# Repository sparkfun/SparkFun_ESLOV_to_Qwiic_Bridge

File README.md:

SparkFun ESLOV to Qwiic Bridge
========================================

[*SparkFun ESLOV to Qwiic Bridge (BOB-23589)*](https://www.sparkfun.com/products/23589)

The SparkFun ESLOV to Qwiic Bridge lets you quickly and easily connect Qwiic breakouts to Arduino boards with an ESLOV connector for I2C communication. ESLOV and Qwiic allow for simple assembly of I2C circuits without requiring soldering.

The ESLOV to Qwiic Bridge includes one Qwiic connector and one ESLOV connector, along with a plated through hole for the interrupt pin on the ESLOV connection. Since the ESLOV connectors have 5V for power, this bridge board includes a voltage regulator to drop that 5V down to 3.3V, making it safe for any Qwiic device.

Repository Contents
-------------------

* **/Documentation** - Data sheets, additional product information
* **/Hardware** - Eagle design files (.brd, .sch)
* **/Production** - Production panel files (.brd)

Product Versions
----------------
* [BOB-23589](https://www.sparkfun.com/products/23589) - Initial release of SparkFun ESLOV to Qwiic Bridge

License Information
-------------------

This product is _**open source**_! 

Please review the LICENSE.md file for license information. 

If you have any questions or concerns on licensing, please contact technical support on our [SparkFun forums](https://forum.sparkfun.com/viewforum.php?f=152).

Distributed as-is; no warranty is given.

- Your friends at SparkFun.

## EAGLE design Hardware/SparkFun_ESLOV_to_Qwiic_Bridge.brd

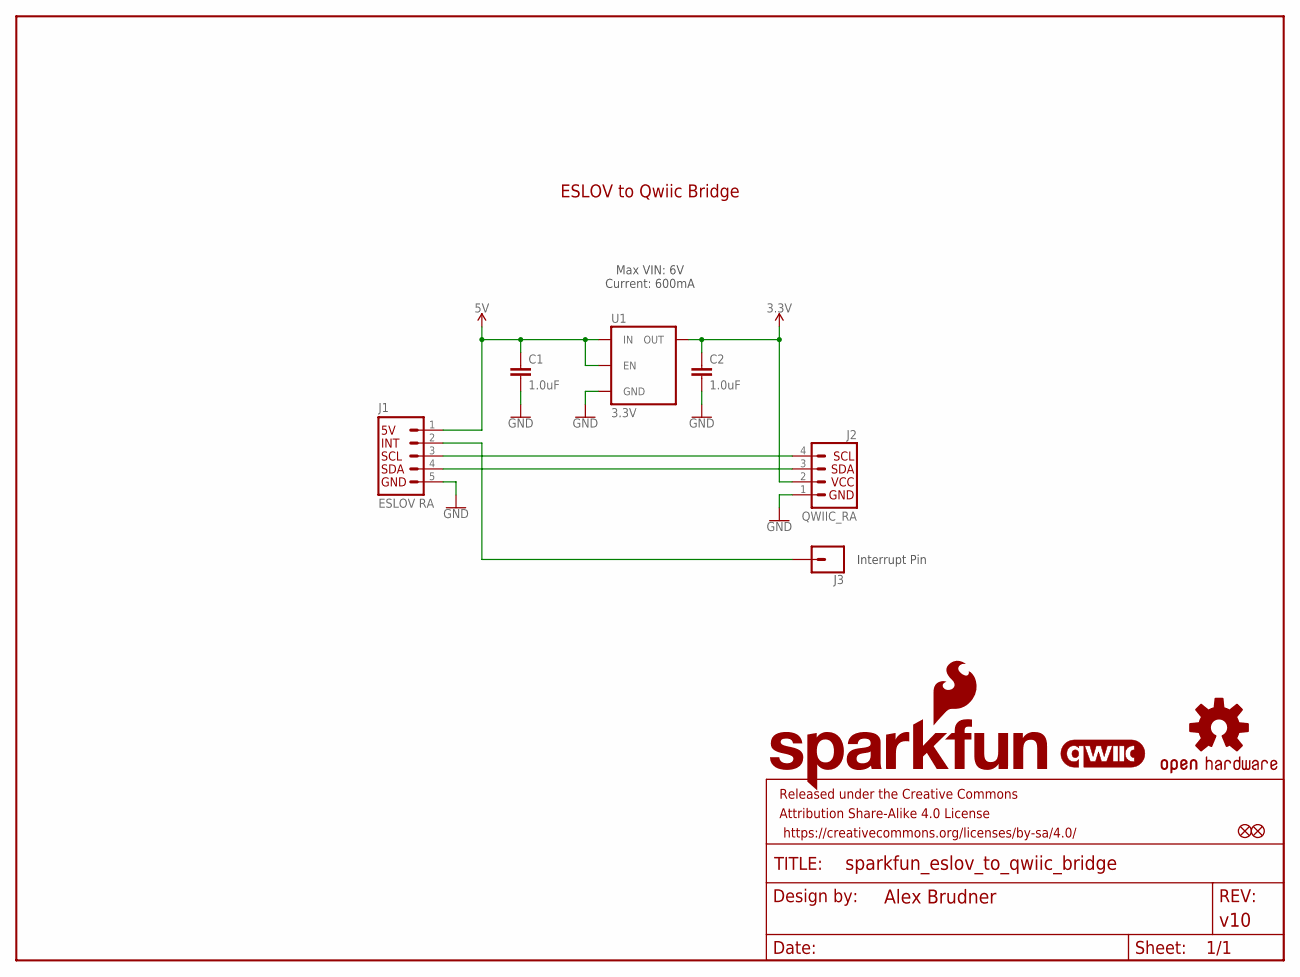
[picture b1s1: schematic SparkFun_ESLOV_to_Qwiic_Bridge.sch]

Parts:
C1, C2: 1.0uF; 0402-TIGHT
FD1, FD2: FIDUCIALUFIDUCIAL; FIDUCIAL-MICRO
FRAME1: FRAME-LETTER; CREATIVE_COMMONS
J1: ESLOV RA; JST_5_1MM_RA
J2: QWIIC_RA; JST04_1MM_RA
J3: CONN_01; 1X01
LOGO1: SFE_LOGO_NAME_FLAME.1_INCH; SFE_LOGO_NAME_FLAME_.1
LOGO2: OSHW-LOGOMINI; OSHW-LOGO-MINI
LOGO3: QWIIC_LOGO_CONNECTOR; QWIIC_5.5MM
U1: 3.3V; SOT23-5

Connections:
3.3V: C2.1, J2.2, U1.5 (OUT)
5V: C1.1, J1.1, U1.1 (IN), U1.3 (EN)
GND: C1.2, C2.2, J1.5, J2.1, U1.2 (GND)
INT: J1.2, J3.1
SCL: J1.3, J2.4
SDA: J1.4, J2.3

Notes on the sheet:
ESLOV to Qwiic Bridge
Interrupt Pin
Max VIN: 6V Current: 600mA

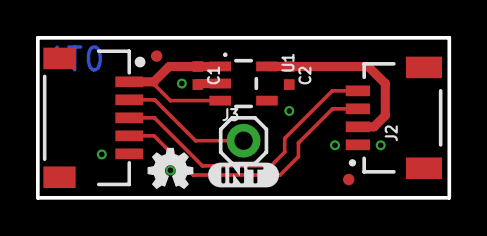
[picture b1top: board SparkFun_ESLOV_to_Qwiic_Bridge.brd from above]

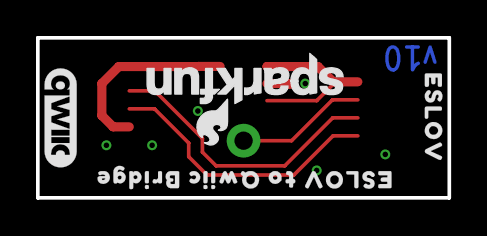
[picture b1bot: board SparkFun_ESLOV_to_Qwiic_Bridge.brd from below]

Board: 2 copper layers, 22.9 x 8.9 mm, 17 parts (4 on the bottom side), 6 nets.

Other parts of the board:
U$1: #INT#0
U$2: ESLOV0
U$3: SFE_LOGO_FLAME_STOP_.1
U$4: ESLOV_TO_QWIIC_BRIDGE0
U$5: ORDERING_INSTRUCTIONS

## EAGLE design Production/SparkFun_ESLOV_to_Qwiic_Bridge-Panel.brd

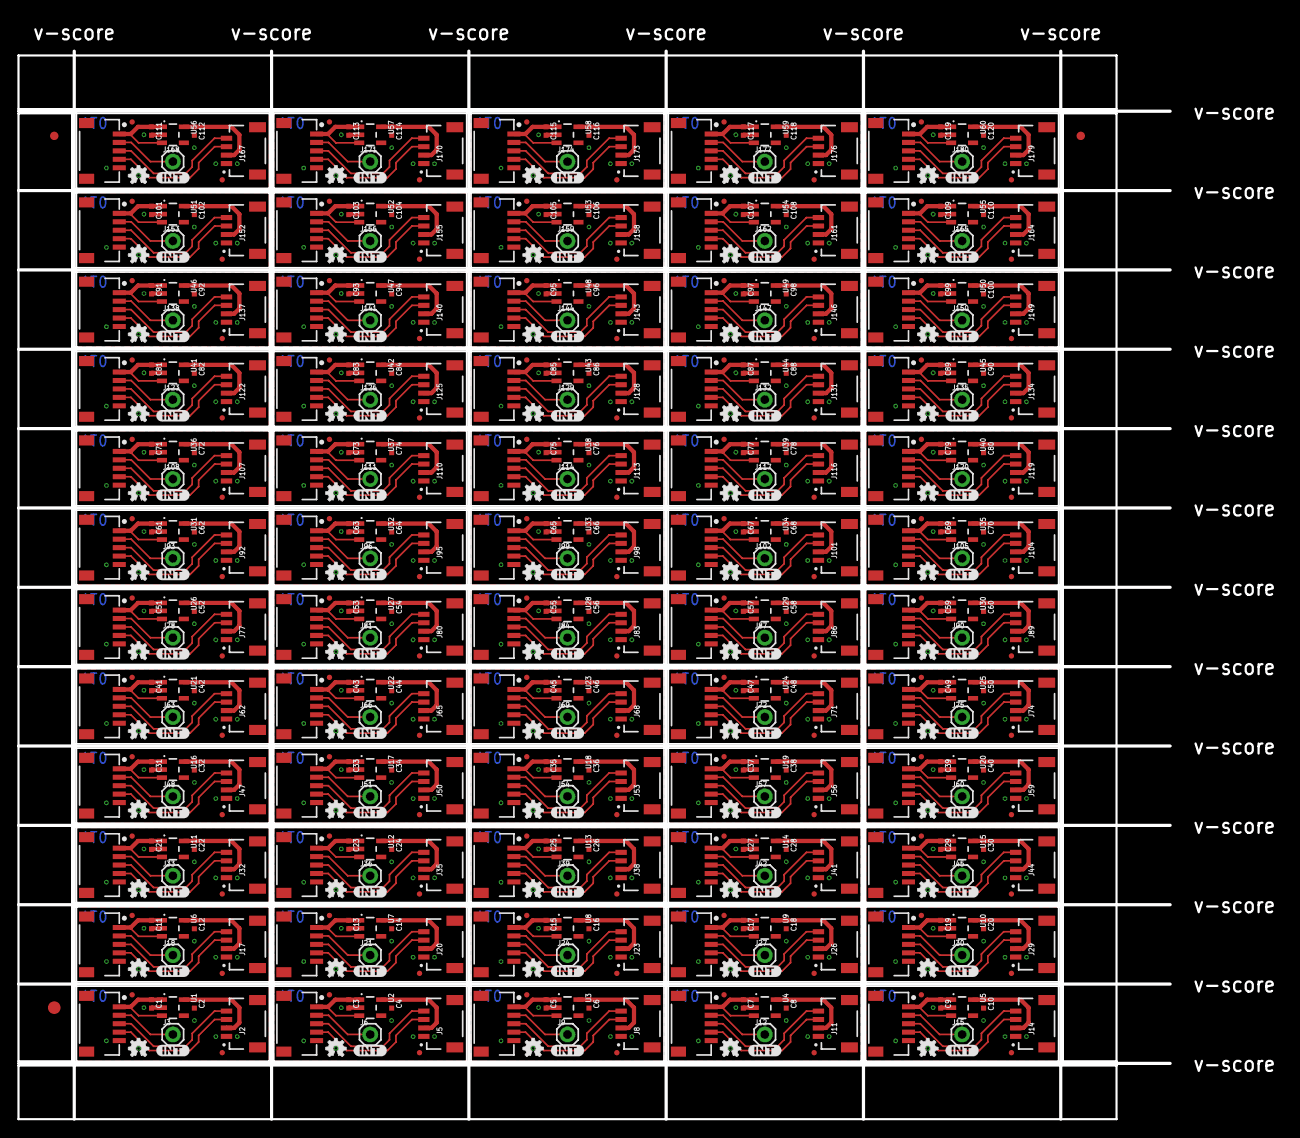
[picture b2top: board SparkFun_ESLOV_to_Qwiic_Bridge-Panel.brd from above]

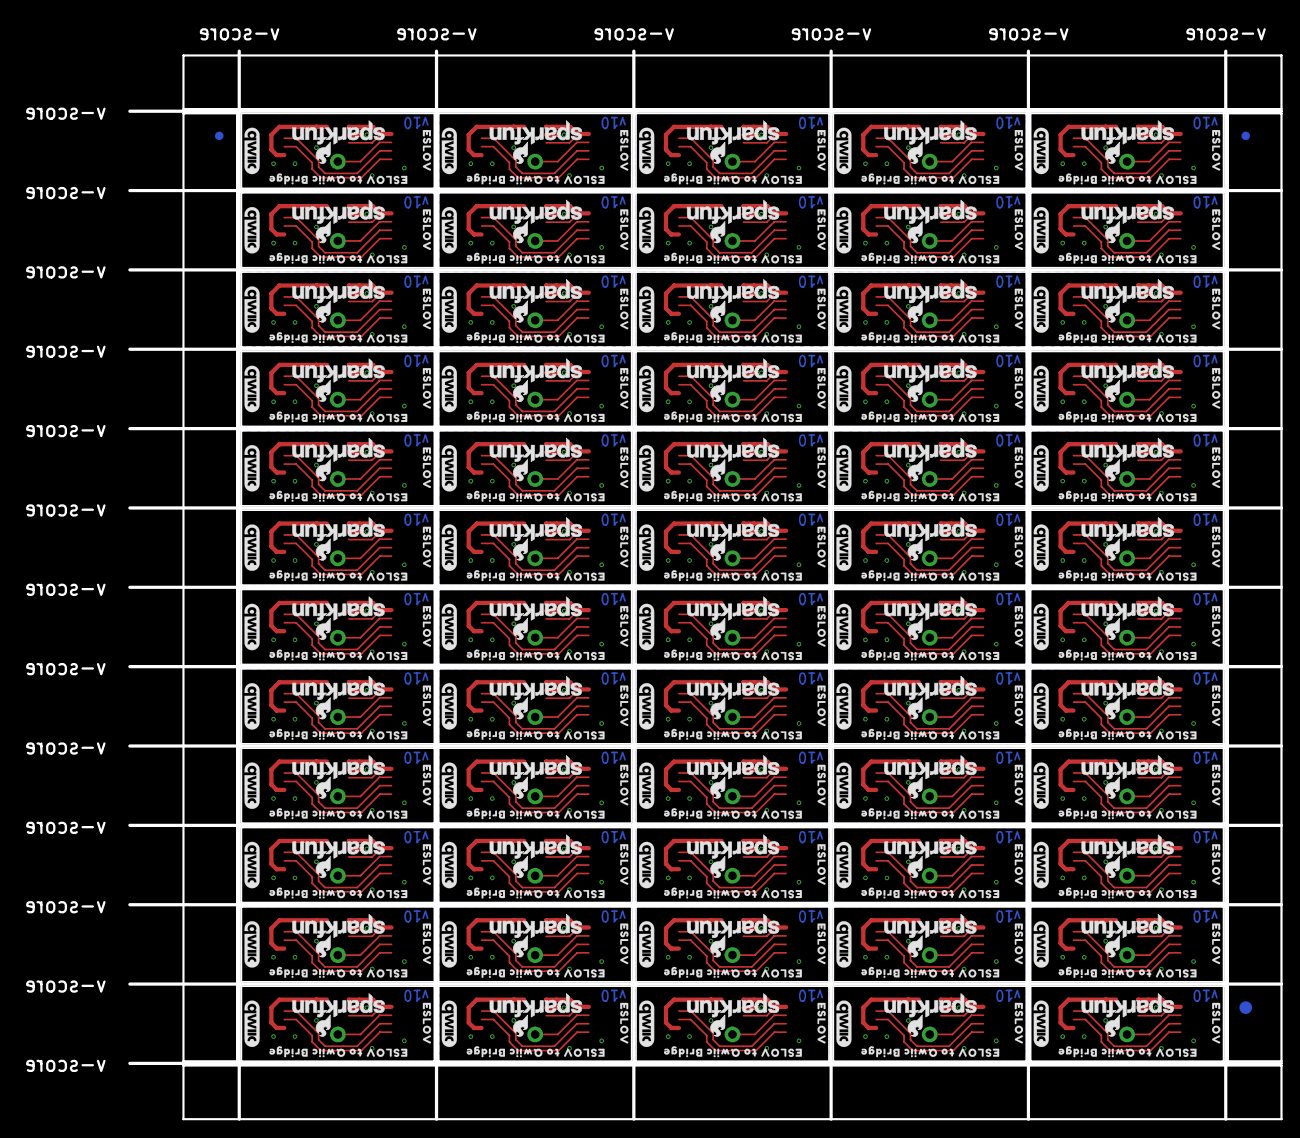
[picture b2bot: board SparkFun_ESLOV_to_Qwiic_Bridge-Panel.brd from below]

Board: 2 copper layers, 136.4 x 126.5 mm, 906 parts (243 on the bottom side), 360 nets.

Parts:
C1, C2, C3, C4, C5, C6, C7, C8, C9, C10, C11, C12, C13, C14, C15, C16, C17, C18, C19, C20, C21, C22, C23, C24, C25, C26, C27, C28, C29, C30, C31, C32, C33, C34, C35, C36, C37, C38, C39, C40, C41, C42, C43, C44, C45, C46, C47, C48, C49, C50, C51, C52, C53, C54, C55, C56, C57, C58, C59, C60, C61, C62, C63, C64, C65, C66, C67, C68, C69, C70, C71, C72, C73, C74, C75, C76, C77, C78, C79, C80, C81, C82, C83, C84, C85, C86, C87, C88, C89, C90, C91, C92, C93, C94, C95, C96, C97, C98, C99, C100, C101, C102, C103, C104, C105, C106, C107, C108, C109, C110, C111, C112, C113, C114, C115, C116, C117, C118, C119, C120: 1.0uF; 0402-TIGHT
E$1, E$2, E$3, E$4: FIDUCIAL-1X2
E$5, E$6: FIDUCIAL-1.5X3
FD1, FD2, FD3, FD4, FD5, FD6, FD7, FD8, FD9, FD10, FD11, FD12, FD13, FD14, FD15, FD16, FD17, FD18, FD19, FD20, FD21, FD22, FD23, FD24, FD25, FD26, FD27, FD28, FD29, FD30, FD31, FD32, FD33, FD34, FD35, FD36, FD37, FD38, FD39, FD40, FD41, FD42, FD43, FD44, FD45, FD46, FD47, FD48, FD49, FD50, FD51, FD52, FD53, FD54, FD55, FD56, FD57, FD58, FD59, FD60, FD61, FD62, FD63, FD64, FD65, FD66, FD67, FD68, FD69, FD70, FD71, FD72, FD73, FD74, FD75, FD76, FD77, FD78, FD79, FD80, FD81, FD82, FD83, FD84, FD85, FD86, FD87, FD88, FD89, FD90, FD91, FD92, FD93, FD94, FD95, FD96, FD97, FD98, FD99, FD100, FD101, FD102, FD103, FD104, FD105, FD106, FD107, FD108, FD109, FD110, FD111, FD112, FD113, FD114, FD115, FD116, FD117, FD118, FD119, FD120: FIDUCIALUFIDUCIAL; FIDUCIAL-MICRO
J1, J4, J7, J10, J13, J16, J19, J22, J25, J28, J31, J34, J37, J40, J43, J46, J49, J52, J55, J58, J61, J64, J67, J70, J73, J76, J79, J82, J85, J88, J91, J94, J97, J100, J103, J106, J109, J112, J115, J118, J121, J124, J127, J130, J133, J136, J139, J142, J145, J148, J151, J154, J157, J160, J163, J166, J169, J172, J175, J178: ESLOV RA; JST_5_1MM_RA
J2, J5, J8, J11, J14, J17, J20, J23, J26, J29, J32, J35, J38, J41, J44, J47, J50, J53, J56, J59, J62, J65, J68, J71, J74, J77, J80, J83, J86, J89, J92, J95, J98, J101, J104, J107, J110, J113, J116, J119, J122, J125, J128, J131, J134, J137, J140, J143, J146, J149, J152, J155, J158, J161, J164, J167, J170, J173, J176, J179: QWIIC_RA; JST04_1MM_RA
J3, J6, J9, J12, J15, J18, J21, J24, J27, J30, J33, J36, J39, J42, J45, J48, J51, J54, J57, J60, J63, J66, J69, J72, J75, J78, J81, J84, J87, J90, J93, J96, J99, J102, J105, J108, J111, J114, J117, J120, J123, J126, J129, J132, J135, J138, J141, J144, J147, J150, J153, J156, J159, J162, J165, J168, J171, J174, J177, J180: 1X01
LOGO1, LOGO4, LOGO7, LOGO10, LOGO13, LOGO16, LOGO19, LOGO22, LOGO25, LOGO28, LOGO31, LOGO34, LOGO37, LOGO40, LOGO43, LOGO46, LOGO49, LOGO52, LOGO55, LOGO58, LOGO61, LOGO64, LOGO67, LOGO70, LOGO73, LOGO76, LOGO79, LOGO82, LOGO85, LOGO88, LOGO91, LOGO94, LOGO97, LOGO100, LOGO103, LOGO106, LOGO109, LOGO112, LOGO115, LOGO118, LOGO121, LOGO124, LOGO127, LOGO130, LOGO133, LOGO136, LOGO139, LOGO142, LOGO145, LOGO148, LOGO151, LOGO154, LOGO157, LOGO160, LOGO163, LOGO166, LOGO169, LOGO172, LOGO175, LOGO178: SFE_LOGO_NAME_FLAME.1_INCH; SFE_LOGO_NAME_FLAME_.1
LOGO2, LOGO5, LOGO8, LOGO11, LOGO14, LOGO17, LOGO20, LOGO23, LOGO26, LOGO29, LOGO32, LOGO35, LOGO38, LOGO41, LOGO44, LOGO47, LOGO50, LOGO53, LOGO56, LOGO59, LOGO62, LOGO65, LOGO68, LOGO71, LOGO74, LOGO77, LOGO80, LOGO83, LOGO86, LOGO89, LOGO92, LOGO95, LOGO98, LOGO101, LOGO104, LOGO107, LOGO110, LOGO113, LOGO116, LOGO119, LOGO122, LOGO125, LOGO128, LOGO131, LOGO134, LOGO137, LOGO140, LOGO143, LOGO146, LOGO149, LOGO152, LOGO155, LOGO158, LOGO161, LOGO164, LOGO167, LOGO170, LOGO173, LOGO176, LOGO179: OSHW-LOGOMINI; OSHW-LOGO-MINI
LOGO3, LOGO6, LOGO9, LOGO12, LOGO15, LOGO18, LOGO21, LOGO24, LOGO27, LOGO30, LOGO33, LOGO36, LOGO39, LOGO42, LOGO45, LOGO48, LOGO51, LOGO54, LOGO57, LOGO60, LOGO63, LOGO66, LOGO69, LOGO72, LOGO75, LOGO78, LOGO81, LOGO84, LOGO87, LOGO90, LOGO93, LOGO96, LOGO99, LOGO102, LOGO105, LOGO108, LOGO111, LOGO114, LOGO117, LOGO120, LOGO123, LOGO126, LOGO129, LOGO132, LOGO135, LOGO138, LOGO141, LOGO144, LOGO147, LOGO150, LOGO153, LOGO156, LOGO159, LOGO162, LOGO165, LOGO168, LOGO171, LOGO174, LOGO177, LOGO180: QWIIC_LOGO_CONNECTOR; QWIIC_5.5MM
U1, U2, U3, U4, U5, U6, U7, U8, U9, U10, U11, U12, U13, U14, U15, U16, U17, U18, U19, U20, U21, U22, U23, U24, U25, U26, U27, U28, U29, U30, U31, U32, U33, U34, U35, U36, U37, U38, U39, U40, U41, U42, U43, U44, U45, U46, U47, U48, U49, U50, U51, U52, U53, U54, U55, U56, U57, U58, U59, U60: 3.3V; SOT23-5
U$1, U$5, U$9, U$13, U$17, U$21, U$25, U$29, U$33, U$37, U$41, U$45, U$49, U$53, U$57, U$61, U$65, U$69, U$73, U$77, U$81, U$85, U$89, U$93, U$97, U$101, U$105, U$109, U$113, U$117, U$121, U$125, U$129, U$133, U$137, U$141, U$145, U$149, U$153, U$157, U$161, U$165, U$169, U$173, U$177, U$181, U$185, U$189, U$193, U$197, U$201, U$205, U$209, U$213, U$217, U$221, U$225, U$229, U$233, U$237: #INT#0
U$2, U$7, U$11, U$15, U$19, U$23, U$27, U$31, U$35, U$39, U$43, U$47, U$51, U$55, U$59, U$63, U$67, U$71, U$75, U$79, U$83, U$87, U$91, U$95, U$99, U$103, U$107, U$111, U$115, U$119, U$123, U$127, U$131, U$135, U$139, U$143, U$147, U$151, U$155, U$159, U$163, U$167, U$171, U$175, U$179, U$183, U$187, U$191, U$195, U$199, U$203, U$207, U$211, U$215, U$219, U$223, U$227, U$231, U$235, U$239: ESLOV0
U$3, U$6, U$10, U$14, U$18, U$22, U$26, U$30, U$34, U$38, U$42, U$46, U$50, U$54, U$58, U$62, U$66, U$70, U$74, U$78, U$82, U$86, U$90, U$94, U$98, U$102, U$106, U$110, U$114, U$118, U$122, U$126, U$130, U$134, U$138, U$142, U$146, U$150, U$154, U$158, U$162, U$166, U$170, U$174, U$178, U$182, U$186, U$190, U$194, U$198, U$202, U$206, U$210, U$214, U$218, U$222, U$226, U$230, U$234, U$238: SFE_LOGO_FLAME_STOP_.1
U$4, U$8, U$12, U$16, U$20, U$24, U$28, U$32, U$36, U$40, U$44, U$48, U$52, U$56, U$60, U$64, U$68, U$72, U$76, U$80, U$84, U$88, U$92, U$96, U$100, U$104, U$108, U$112, U$116, U$120, U$124, U$128, U$132, U$136, U$140, U$144, U$148, U$152, U$156, U$160, U$164, U$168, U$172, U$176, U$180, U$184, U$188, U$192, U$196, U$200, U$204, U$208, U$212, U$216, U$220, U$224, U$228, U$232, U$236, U$240: ESLOV_TO_QWIIC_BRIDGE0

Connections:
3.3V: C2.1, J2.2, U1.5
3.3V1: C4.1, J5.2, U2.5
3.3V2: C6.1, J8.2, U3.5
3.3V3: C8.1, J11.2, U4.5
3.3V4: C10.1, J14.2, U5.5
3.3V5: C12.1, J17.2, U6.5
3.3V6: C14.1, J20.2, U7.5
3.3V7: C16.1, J23.2, U8.5
3.3V8: C18.1, J26.2, U9.5
3.3V9: C20.1, J29.2, U10.5
3.3V10: C22.1, J32.2, U11.5
3.3V11: C24.1, J35.2, U12.5
3.3V12: C26.1, J38.2, U13.5
3.3V13: C28.1, J41.2, U14.5
3.3V14: C30.1, J44.2, U15.5
3.3V15: C32.1, J47.2, U16.5
3.3V16: C34.1, J50.2, U17.5
3.3V17: C36.1, J53.2, U18.5
3.3V18: C38.1, J56.2, U19.5
3.3V19: C40.1, J59.2, U20.5
3.3V20: C42.1, J62.2, U21.5
3.3V21: C44.1, J65.2, U22.5
3.3V22: C46.1, J68.2, U23.5
3.3V23: C48.1, J71.2, U24.5
3.3V24: C50.1, J74.2, U25.5
3.3V25: C52.1, J77.2, U26.5
3.3V26: C54.1, J80.2, U27.5
3.3V27: C56.1, J83.2, U28.5
3.3V28: C58.1, J86.2, U29.5
3.3V29: C60.1, J89.2, U30.5
3.3V30: C62.1, J92.2, U31.5
3.3V31: C64.1, J95.2, U32.5
3.3V32: C66.1, J98.2, U33.5
3.3V33: C68.1, J101.2, U34.5
3.3V34: C70.1, J104.2, U35.5
3.3V35: C72.1, J107.2, U36.5
3.3V36: C74.1, J110.2, U37.5
3.3V37: C76.1, J113.2, U38.5
3.3V38: C78.1, J116.2, U39.5
3.3V39: C80.1, J119.2, U40.5
3.3V40: C82.1, J122.2, U41.5
3.3V41: C84.1, J125.2, U42.5
3.3V42: C86.1, J128.2, U43.5
3.3V43: C88.1, J131.2, U44.5
3.3V44: C90.1, J134.2, U45.5
3.3V45: C92.1, J137.2, U46.5
3.3V46: C94.1, J140.2, U47.5
3.3V47: C96.1, J143.2, U48.5
3.3V48: C98.1, J146.2, U49.5
3.3V49: C100.1, J149.2, U50.5
3.3V50: C102.1, J152.2, U51.5
3.3V51: C104.1, J155.2, U52.5
3.3V52: C106.1, J158.2, U53.5
3.3V53: C108.1, J161.2, U54.5
3.3V54: C110.1, J164.2, U55.5
3.3V55: C112.1, J167.2, U56.5
3.3V56: C114.1, J170.2, U57.5
3.3V57: C116.1, J173.2, U58.5
3.3V58: C118.1, J176.2, U59.5
3.3V59: C120.1, J179.2, U60.5
5V: C1.1, J1.1, U1.1, U1.3
5V1: C3.1, J4.1, U2.1, U2.3
5V2: C5.1, J7.1, U3.1, U3.3
5V3: C7.1, J10.1, U4.1, U4.3
5V4: C9.1, J13.1, U5.1, U5.3
5V5: C11.1, J16.1, U6.1, U6.3
5V6: C13.1, J19.1, U7.1, U7.3
5V7: C15.1, J22.1, U8.1, U8.3
5V8: C17.1, J25.1, U9.1, U9.3
5V9: C19.1, J28.1, U10.1, U10.3
5V10: C21.1, J31.1, U11.1, U11.3
5V11: C23.1, J34.1, U12.1, U12.3
5V12: C25.1, J37.1, U13.1, U13.3
5V13: C27.1, J40.1, U14.1, U14.3
5V14: C29.1, J43.1, U15.1, U15.3
5V15: C31.1, J46.1, U16.1, U16.3
5V16: C33.1, J49.1, U17.1, U17.3
5V17: C35.1, J52.1, U18.1, U18.3
5V18: C37.1, J55.1, U19.1, U19.3
5V19: C39.1, J58.1, U20.1, U20.3
5V20: C41.1, J61.1, U21.1, U21.3
5V21: C43.1, J64.1, U22.1, U22.3
5V22: C45.1, J67.1, U23.1, U23.3
5V23: C47.1, J70.1, U24.1, U24.3
5V24: C49.1, J73.1, U25.1, U25.3
5V25: C51.1, J76.1, U26.1, U26.3
5V26: C53.1, J79.1, U27.1, U27.3
5V27: C55.1, J82.1, U28.1, U28.3
5V28: C57.1, J85.1, U29.1, U29.3
5V29: C59.1, J88.1, U30.1, U30.3
5V30: C61.1, J91.1, U31.1, U31.3
5V31: C63.1, J94.1, U32.1, U32.3
5V32: C65.1, J97.1, U33.1, U33.3
5V33: C67.1, J100.1, U34.1, U34.3
5V34: C69.1, J103.1, U35.1, U35.3
5V35: C71.1, J106.1, U36.1, U36.3
5V36: C73.1, J109.1, U37.1, U37.3
5V37: C75.1, J112.1, U38.1, U38.3
5V38: C77.1, J115.1, U39.1, U39.3
5V39: C79.1, J118.1, U40.1, U40.3
5V40: C81.1, J121.1, U41.1, U41.3
5V41: C83.1, J124.1, U42.1, U42.3
5V42: C85.1, J127.1, U43.1, U43.3
5V43: C87.1, J130.1, U44.1, U44.3
5V44: C89.1, J133.1, U45.1, U45.3
5V45: C91.1, J136.1, U46.1, U46.3
5V46: C93.1, J139.1, U47.1, U47.3
5V47: C95.1, J142.1, U48.1, U48.3
5V48: C97.1, J145.1, U49.1, U49.3
5V49: C99.1, J148.1, U50.1, U50.3
5V50: C101.1, J151.1, U51.1, U51.3
5V51: C103.1, J154.1, U52.1, U52.3
5V52: C105.1, J157.1, U53.1, U53.3
5V53: C107.1, J160.1, U54.1, U54.3
5V54: C109.1, J163.1, U55.1, U55.3
5V55: C111.1, J166.1, U56.1, U56.3
5V56: C113.1, J169.1, U57.1, U57.3
5V57: C115.1, J172.1, U58.1, U58.3
5V58: C117.1, J175.1, U59.1, U59.3
5V59: C119.1, J178.1, U60.1, U60.3
GND: C1.2, C2.2, J1.5, J2.1, U1.2
GND1: C3.2, C4.2, J4.5, J5.1, U2.2
GND2: C5.2, C6.2, J7.5, J8.1, U3.2
GND3: C7.2, C8.2, J10.5, J11.1, U4.2
GND4: C9.2, C10.2, J13.5, J14.1, U5.2
GND5: C11.2, C12.2, J16.5, J17.1, U6.2
GND6: C13.2, C14.2, J19.5, J20.1, U7.2
GND7: C15.2, C16.2, J22.5, J23.1, U8.2
GND8: C17.2, C18.2, J25.5, J26.1, U9.2
GND9: C19.2, C20.2, J28.5, J29.1, U10.2
GND10: C21.2, C22.2, J31.5, J32.1, U11.2
GND11: C23.2, C24.2, J34.5, J35.1, U12.2
GND12: C25.2, C26.2, J37.5, J38.1, U13.2
GND13: C27.2, C28.2, J40.5, J41.1, U14.2
GND14: C29.2, C30.2, J43.5, J44.1, U15.2
GND15: C31.2, C32.2, J46.5, J47.1, U16.2
GND16: C33.2, C34.2, J49.5, J50.1, U17.2
GND17: C35.2, C36.2, J52.5, J53.1, U18.2
GND18: C37.2, C38.2, J55.5, J56.1, U19.2
GND19: C39.2, C40.2, J58.5, J59.1, U20.2
GND20: C41.2, C42.2, J61.5, J62.1, U21.2
GND21: C43.2, C44.2, J64.5, J65.1, U22.2
GND22: C45.2, C46.2, J67.5, J68.1, U23.2
GND23: C47.2, C48.2, J70.5, J71.1, U24.2
GND24: C49.2, C50.2, J73.5, J74.1, U25.2
GND25: C51.2, C52.2, J76.5, J77.1, U26.2
GND26: C53.2, C54.2, J79.5, J80.1, U27.2
GND27: C55.2, C56.2, J82.5, J83.1, U28.2
GND28: C57.2, C58.2, J85.5, J86.1, U29.2
GND29: C59.2, C60.2, J88.5, J89.1, U30.2
GND30: C61.2, C62.2, J91.5, J92.1, U31.2
GND31: C63.2, C64.2, J94.5, J95.1, U32.2
GND32: C65.2, C66.2, J97.5, J98.1, U33.2
GND33: C67.2, C68.2, J100.5, J101.1, U34.2
GND34: C69.2, C70.2, J103.5, J104.1, U35.2
GND35: C71.2, C72.2, J106.5, J107.1, U36.2
GND36: C73.2, C74.2, J109.5, J110.1, U37.2
GND37: C75.2, C76.2, J112.5, J113.1, U38.2
GND38: C77.2, C78.2, J115.5, J116.1, U39.2
GND39: C79.2, C80.2, J118.5, J119.1, U40.2
GND40: C81.2, C82.2, J121.5, J122.1, U41.2
GND41: C83.2, C84.2, J124.5, J125.1, U42.2
GND42: C85.2, C86.2, J127.5, J128.1, U43.2
GND43: C87.2, C88.2, J130.5, J131.1, U44.2
GND44: C89.2, C90.2, J133.5, J134.1, U45.2
GND45: C91.2, C92.2, J136.5, J137.1, U46.2
GND46: C93.2, C94.2, J139.5, J140.1, U47.2
GND47: C95.2, C96.2, J142.5, J143.1, U48.2
GND48: C97.2, C98.2, J145.5, J146.1, U49.2
GND49: C99.2, C100.2, J148.5, J149.1, U50.2
GND50: C101.2, C102.2, J151.5, J152.1, U51.2
GND51: C103.2, C104.2, J154.5, J155.1, U52.2
GND52: C105.2, C106.2, J157.5, J158.1, U53.2
GND53: C107.2, C108.2, J160.5, J161.1, U54.2
GND54: C109.2, C110.2, J163.5, J164.1, U55.2
GND55: C111.2, C112.2, J166.5, J167.1, U56.2
GND56: C113.2, C114.2, J169.5, J170.1, U57.2
GND57: C115.2, C116.2, J172.5, J173.1, U58.2
GND58: C117.2, C118.2, J175.5, J176.1, U59.2
GND59: C119.2, C120.2, J178.5, J179.1, U60.2
INT: J1.2, J3.1
INT1: J4.2, J6.1
INT2: J7.2, J9.1
INT3: J10.2, J12.1
INT4: J13.2, J15.1
INT5: J16.2, J18.1
INT6: J19.2, J21.1
INT7: J22.2, J24.1
INT8: J25.2, J27.1
INT9: J28.2, J30.1
INT10: J31.2, J33.1
INT11: J34.2, J36.1
INT12: J37.2, J39.1
INT13: J40.2, J42.1
INT14: J43.2, J45.1
INT15: J46.2, J48.1
INT16: J49.2, J51.1
INT17: J52.2, J54.1
INT18: J55.2, J57.1
INT19: J58.2, J60.1
INT20: J61.2, J63.1
INT21: J64.2, J66.1
INT22: J67.2, J69.1
INT23: J70.2, J72.1
INT24: J73.2, J75.1
INT25: J76.2, J78.1
INT26: J79.2, J81.1
INT27: J82.2, J84.1
INT28: J85.2, J87.1
INT29: J88.2, J90.1
INT30: J91.2, J93.1
INT31: J94.2, J96.1
INT32: J97.2, J99.1
INT33: J100.2, J102.1
INT34: J103.2, J105.1
INT35: J106.2, J108.1
INT36: J109.2, J111.1
INT37: J112.2, J114.1
INT38: J115.2, J117.1
INT39: J118.2, J120.1
INT40: J121.2, J123.1
INT41: J124.2, J126.1
INT42: J127.2, J129.1
INT43: J130.2, J132.1
INT44: J133.2, J135.1
INT45: J136.2, J138.1
INT46: J139.2, J141.1
INT47: J142.2, J144.1
INT48: J145.2, J147.1
INT49: J148.2, J150.1
INT50: J151.2, J153.1
INT51: J154.2, J156.1
INT52: J157.2, J159.1
INT53: J160.2, J162.1
INT54: J163.2, J165.1
INT55: J166.2, J168.1
INT56: J169.2, J171.1
INT57: J172.2, J174.1
INT58: J175.2, J177.1
INT59: J178.2, J180.1
SCL: J1.3, J2.4
SCL1: J4.3, J5.4
SCL2: J7.3, J8.4
SCL3: J10.3, J11.4
SCL4: J13.3, J14.4
SCL5: J16.3, J17.4
SCL6: J19.3, J20.4
SCL7: J22.3, J23.4
SCL8: J25.3, J26.4
SCL9: J28.3, J29.4
SCL10: J31.3, J32.4
SCL11: J34.3, J35.4
SCL12: J37.3, J38.4
SCL13: J40.3, J41.4
SCL14: J43.3, J44.4
SCL15: J46.3, J47.4
SCL16: J49.3, J50.4
SCL17: J52.3, J53.4
SCL18: J55.3, J56.4
SCL19: J58.3, J59.4
SCL20: J61.3, J62.4
SCL21: J64.3, J65.4
SCL22: J67.3, J68.4
SCL23: J70.3, J71.4
SCL24: J73.3, J74.4
SCL25: J76.3, J77.4
SCL26: J79.3, J80.4
SCL27: J82.3, J83.4
SCL28: J85.3, J86.4
SCL29: J88.3, J89.4
SCL30: J91.3, J92.4
SCL31: J94.3, J95.4
SCL32: J97.3, J98.4
SCL33: J100.3, J101.4
SCL34: J103.3, J104.4
SCL35: J106.3, J107.4
SCL36: J109.3, J110.4
SCL37: J112.3, J113.4
SCL38: J115.3, J116.4
SCL39: J118.3, J119.4
SCL40: J121.3, J122.4
SCL41: J124.3, J125.4
SCL42: J127.3, J128.4
SCL43: J130.3, J131.4
SCL44: J133.3, J134.4
SCL45: J136.3, J137.4
SCL46: J139.3, J140.4
SCL47: J142.3, J143.4
SCL48: J145.3, J146.4
SCL49: J148.3, J149.4
SCL50: J151.3, J152.4
SCL51: J154.3, J155.4
SCL52: J157.3, J158.4
SCL53: J160.3, J161.4
SCL54: J163.3, J164.4
SCL55: J166.3, J167.4
SCL56: J169.3, J170.4
SCL57: J172.3, J173.4
SCL58: J175.3, J176.4
SCL59: J178.3, J179.4
SDA: J1.4, J2.3
SDA1: J4.4, J5.3
SDA2: J7.4, J8.3
SDA3: J10.4, J11.3
SDA4: J13.4, J14.3
SDA5: J16.4, J17.3
SDA6: J19.4, J20.3
SDA7: J22.4, J23.3
SDA8: J25.4, J26.3
SDA9: J28.4, J29.3
SDA10: J31.4, J32.3
SDA11: J34.4, J35.3
SDA12: J37.4, J38.3
SDA13: J40.4, J41.3
SDA14: J43.4, J44.3
SDA15: J46.4, J47.3
SDA16: J49.4, J50.3
SDA17: J52.4, J53.3
SDA18: J55.4, J56.3
SDA19: J58.4, J59.3
SDA20: J61.4, J62.3
SDA21: J64.4, J65.3
SDA22: J67.4, J68.3
SDA23: J70.4, J71.3
SDA24: J73.4, J74.3
SDA25: J76.4, J77.3
SDA26: J79.4, J80.3
SDA27: J82.4, J83.3
SDA28: J85.4, J86.3
SDA29: J88.4, J89.3
SDA30: J91.4, J92.3
SDA31: J94.4, J95.3
SDA32: J97.4, J98.3
SDA33: J100.4, J101.3
SDA34: J103.4, J104.3
SDA35: J106.4, J107.3
SDA36: J109.4, J110.3
SDA37: J112.4, J113.3
SDA38: J115.4, J116.3
SDA39: J118.4, J119.3
SDA40: J121.4, J122.3
SDA41: J124.4, J125.3
SDA42: J127.4, J128.3
SDA43: J130.4, J131.3
SDA44: J133.4, J134.3
SDA45: J136.4, J137.3
SDA46: J139.4, J140.3
SDA47: J142.4, J143.3
SDA48: J145.4, J146.3
SDA49: J148.4, J149.3
SDA50: J151.4, J152.3
SDA51: J154.4, J155.3
SDA52: J157.4, J158.3
SDA53: J160.4, J161.3
SDA54: J163.4, J164.3
SDA55: J166.4, J167.3
SDA56: J169.4, J170.3
SDA57: J172.4, J173.3
SDA58: J175.4, J176.3
SDA59: J178.4, J179.3

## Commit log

2023-09-15 Add Connector Datasheet.
2023-09-15 First Draft complete.
2023-09-15 Rename Board File
2023-09-15 Add production files.
2023-11-03 Update README.md
    Update readme from template.

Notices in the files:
parts and their libraries:
SparkFun-Capacitors: Licensing: Creative Commons ShareAlike 4.0 International - https://creativecommons.org/licenses/by-sa/4.0
SparkFun-Aesthetics: Released under the Creative Commons Attribution Share-Alike 4.0 License
SparkFun-Aesthetics: https://creativecommons.org/licenses/by-sa/4.0
